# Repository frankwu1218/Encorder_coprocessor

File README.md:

# Encorder_coprocessor
Encoder coprocessor based on PICO2040

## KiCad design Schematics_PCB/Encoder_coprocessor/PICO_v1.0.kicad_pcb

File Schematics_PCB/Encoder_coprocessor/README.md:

# PICO_Encoder_sensor_PCB
Encoder sensor PCB board

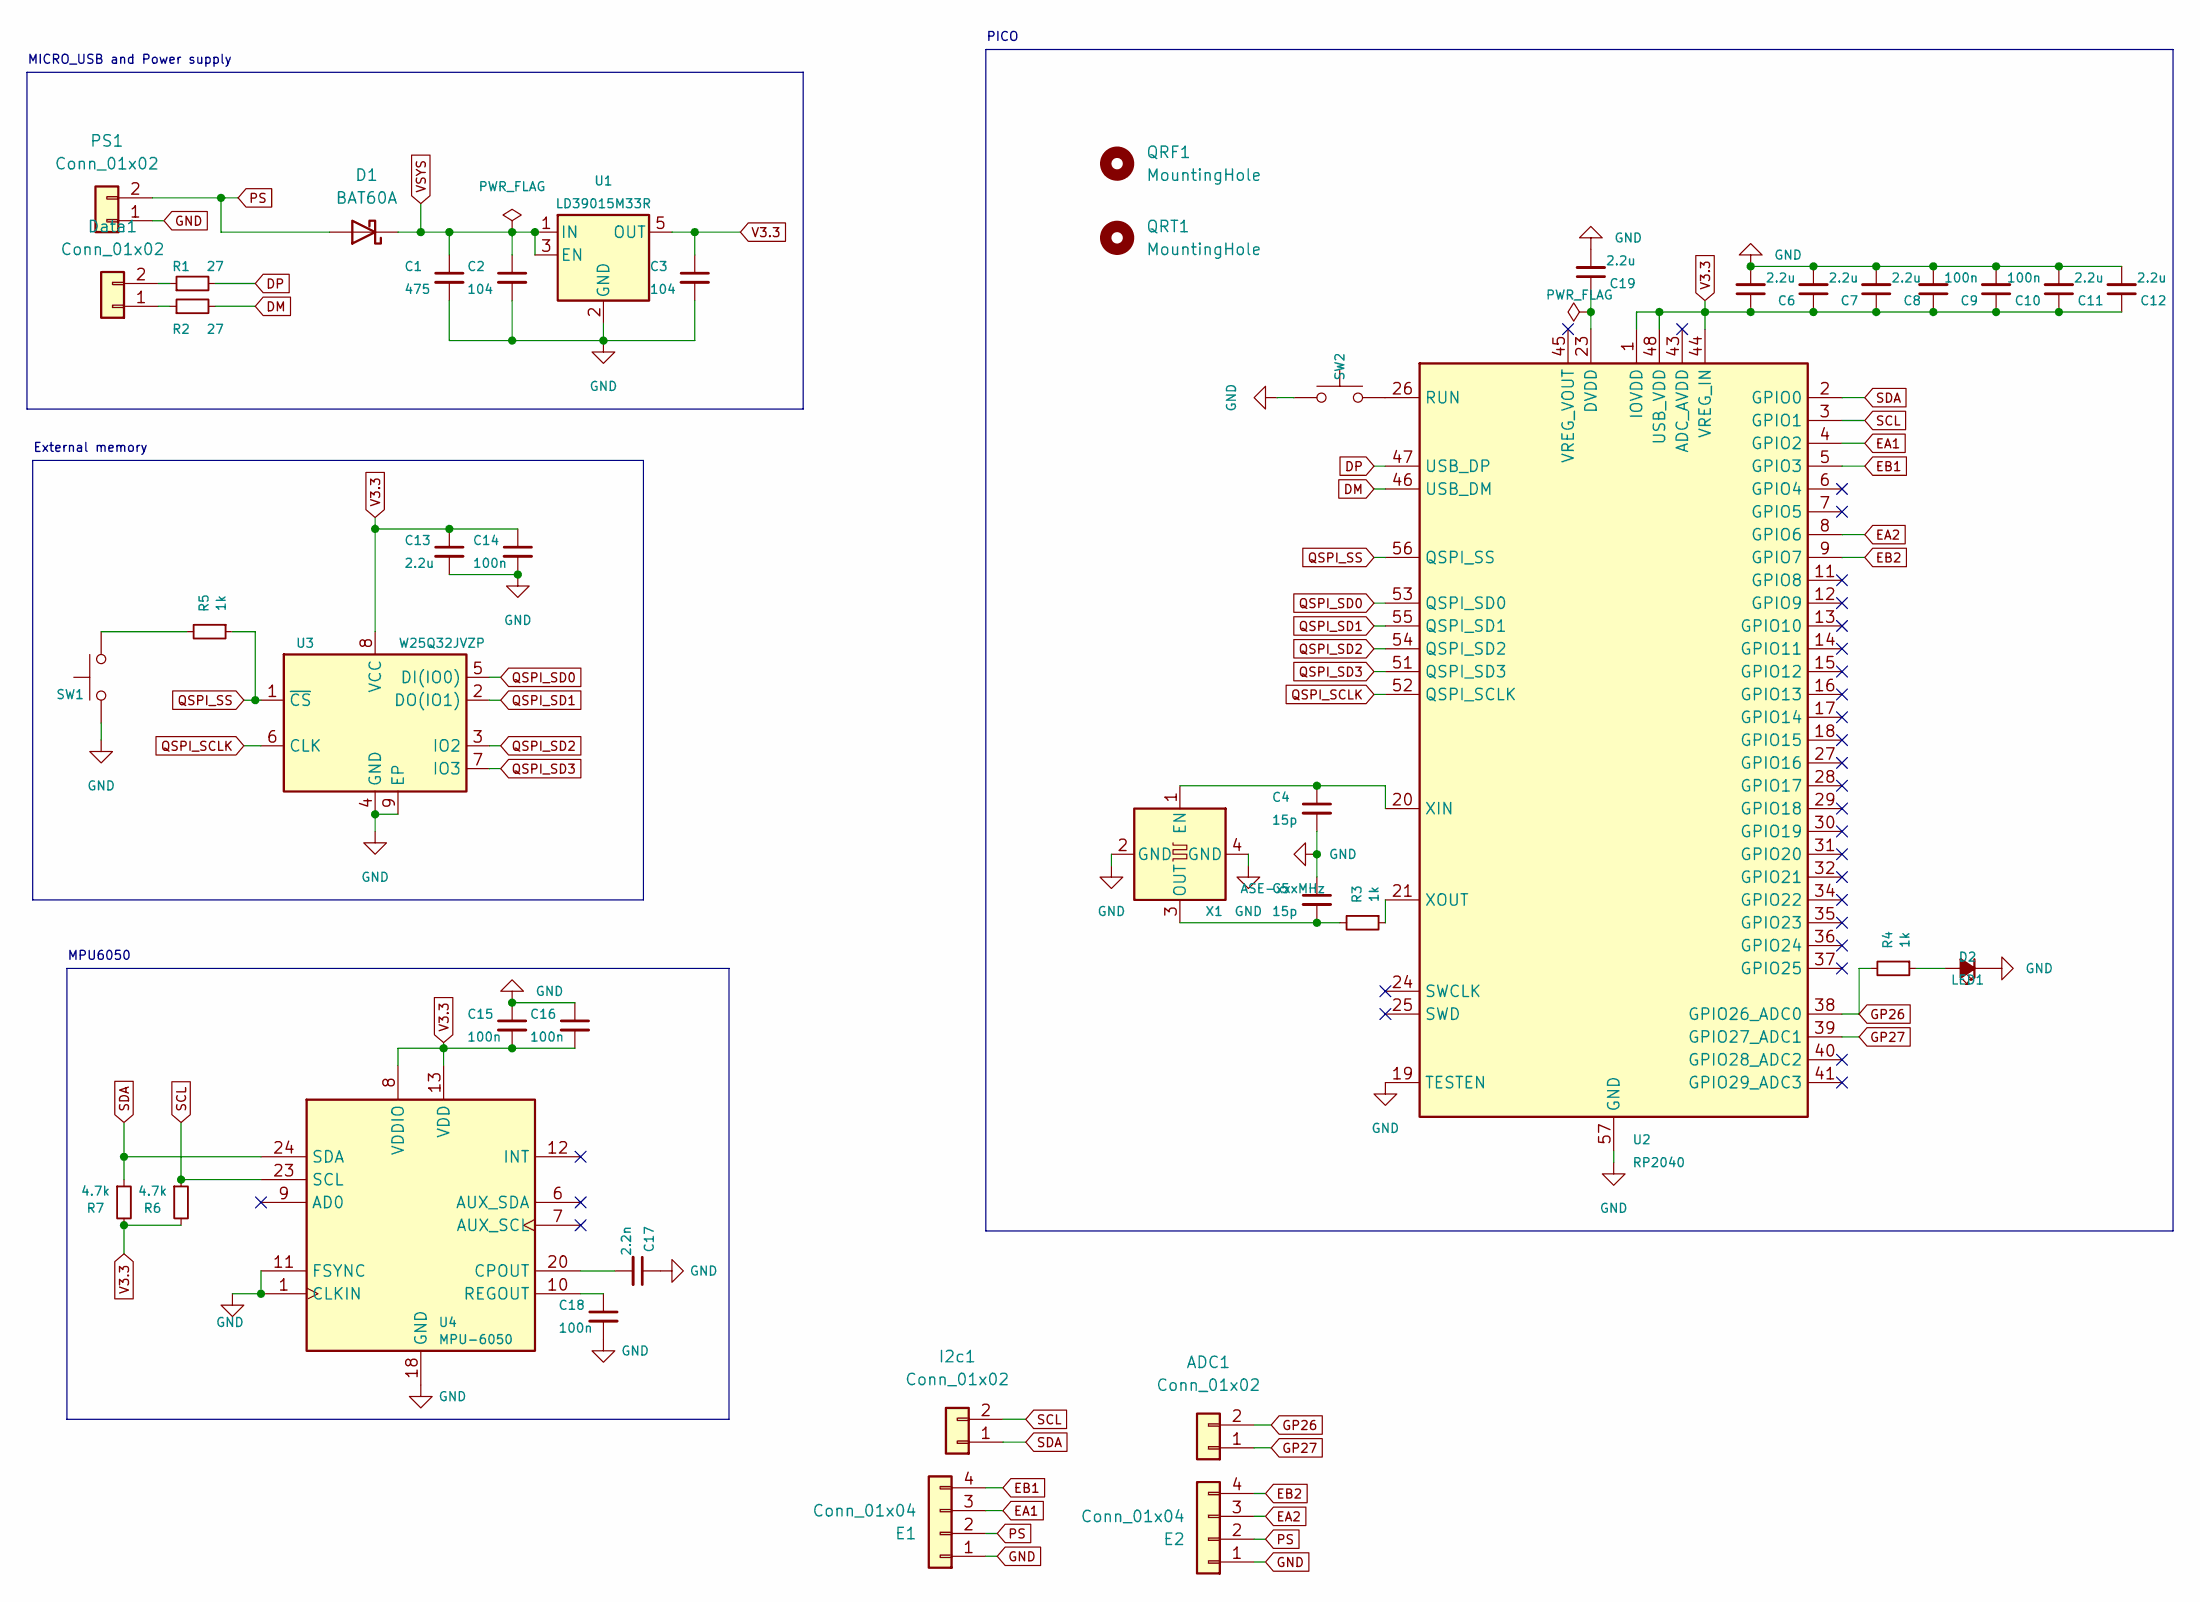
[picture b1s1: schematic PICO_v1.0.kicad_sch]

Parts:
ADC1: Conn_01x02; PinHeader_1x02_P2.54mm_Vertical
C1: 475; C_0603_1608Metric_Pad1.08x0.95mm_HandSolder
C2, C3: 104; C_0603_1608Metric_Pad1.08x0.95mm_HandSolder
C4, C5: 15p; C_0603_1608Metric_Pad1.08x0.95mm_HandSolder
C6, C7, C8, C11, C12, C13, C19: 2.2u; C_0603_1608Metric_Pad1.08x0.95mm_HandSolder
C9, C10, C14, C15, C16, C18: 100n; C_0603_1608Metric_Pad1.08x0.95mm_HandSolder
C17: 2.2n; C_0603_1608Metric_Pad1.08x0.95mm_HandSolder
D1: BAT60A; D_SOD-323
D2: LED1; LED_0603_1608Metric_Pad1.05x0.95mm_HandSolder
Data1: Conn_01x02; PinHeader_1x02_P2.54mm_Vertical
E1, E2: Conn_01x04; PinHeader_1x04_P2.54mm_Vertical
I2c1: Conn_01x02; PinHeader_1x02_P2.54mm_Vertical
PS1: Conn_01x02; PinHeader_1x02_P2.54mm_Vertical
QRF1: MountingHole; Frank_github_5_5
QRT1: MountingHole; Temple_5_5
R1, R2: 27; R_0603_1608Metric_Pad0.98x0.95mm_HandSolder
R3, R5: 1k; R_0603_1608Metric_Pad0.98x0.95mm_HandSolder
R4: 1k; R_0603_1608Metric
R6, R7: 4.7k; R_0603_1608Metric_Pad0.98x0.95mm_HandSolder
SW1, SW2: SW_Push; LED_1210_3225Metric_Pad1.42x2.65mm_HandSolder
U1: LD39015M33R; SOT-23-5
U2: RP2040; QFN-56-1EP_7x7mm_P0.4mm_EP3.2x3.2mm
U3: W25Q32JVZP; WSON-8-1EP_6x5mm_P1.27mm_EP3.4x4.3mm
U4: MPU-6050; InvenSense_QFN-24_4x4mm_P0.5mm
X1: ASE-xxxMHz; Oscillator_SMD_Abracon_ASE-4Pin_3.2x2.5mm

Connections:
DM: R2.2, U2.46 (USB_DM)
DP: R1.2, U2.47 (USB_DP)
EA1: E1.3, U2.4 (GPIO2)
EA2: E2.3, U2.8 (GPIO6)
EB1: E1.4, U2.5 (GPIO3)
EB2: E2.4, U2.9 (GPIO7)
GND: C1.2, C2.2, C3.2, C4.2, C5.1, C6.2, C7.2, C8.2, C9.2, C10.2, C11.2, C12.2, C13.2, C14.2, C15.1, C16.1, C17.1, C18.2, C19.2, D2.1 (K), E1.1, E2.1, PS1.1, SW1.1, SW2.1, U1.2 (GND), U2.19 (TESTEN), U2.57 (GND), U3.4 (GND), U3.9 (EP), U4.1 (CLKIN), U4.11 (FSYNC), U4.18 (GND), X1.2 (GND), X1.4 (GND)
GP26: ADC1.2, R4.2, U2.38 (GPIO26_ADC0)
GP27: ADC1.1, U2.39 (GPIO27_ADC1)
unnamed: C4.1, U2.20 (XIN), X1.1 (EN)
unnamed: C5.2, R3.2, X1.3 (OUT)
unnamed: C17.2, U4.20 (CPOUT)
unnamed: C18.1, U4.10 (REGOUT)
unnamed: C19.1, U2.23 (DVDD), U2.50 (DVDD)
unnamed: D2.2 (A), R4.1
unnamed: Data1.1, R2.1
unnamed: Data1.2, R1.1
unnamed: R3.1, U2.21 (XOUT)
unnamed: R5.2, SW1.2
unnamed: SW2.2, U2.26 (RUN)
PS: D1.2 (A), E1.2, E2.2, PS1.2
QSPI_SCLK: U2.52 (QSPI_SCLK), U3.6 (CLK)
QSPI_SD0: U2.53 (QSPI_SD0), U3.5 (DI(IO0))
QSPI_SD1: U2.55 (QSPI_SD1), U3.2 (DO(IO1))
QSPI_SD2: U2.54 (QSPI_SD2), U3.3 (IO2)
QSPI_SD3: U2.51 (QSPI_SD3), U3.7 (IO3)
QSPI_SS: R5.1, U2.56 (QSPI_SS), U3.1 (~CS)
SCL: I2c1.2, R6.1, U2.3 (GPIO1), U4.23 (SCL)
SDA: I2c1.1, R7.1, U2.2 (GPIO0), U4.24 (SDA)
V3.3: C3.1, C6.1, C7.1, C8.1, C9.1, C10.1, C11.1, C12.1, C13.1, C14.1, C15.2, C16.2, R6.2, R7.2, U1.5 (OUT), U2.1 (IOVDD), U2.10 (IOVDD), U2.22 (IOVDD), U2.33 (IOVDD), U2.42 (IOVDD), U2.44 (VREG_IN), U2.48 (USB_VDD), U2.49 (IOVDD), U3.8 (VCC), U4.8 (VDDIO), U4.13 (VDD)
VSYS: C1.1, C2.1, D1.1 (K), U1.1 (IN), U1.3 (EN)

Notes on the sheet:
MPU6050
MICRO_USB and Power supply
External memory
PICO

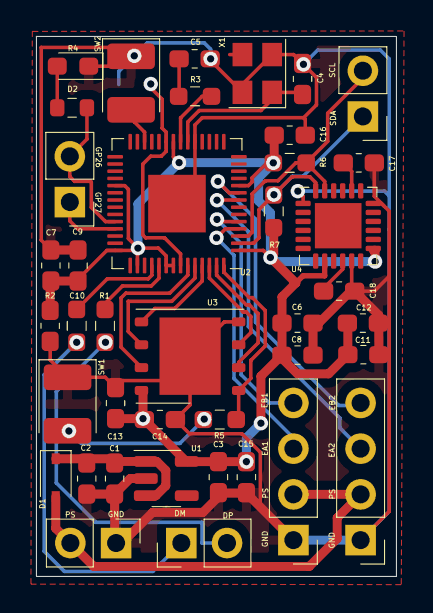
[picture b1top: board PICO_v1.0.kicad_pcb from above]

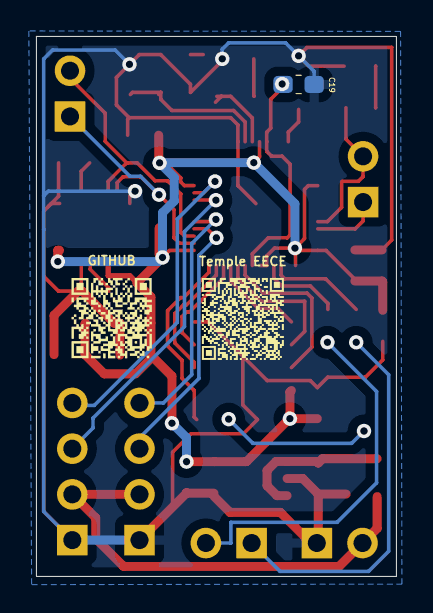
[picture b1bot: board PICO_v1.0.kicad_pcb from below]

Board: 2 copper layers, 20.0 x 30.0 mm, 43 parts (3 on the bottom side), 31 nets.

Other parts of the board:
GITHUB: MountingHole; Frank_github_5_5
Temple EECE: MountingHole; Temple_5_5

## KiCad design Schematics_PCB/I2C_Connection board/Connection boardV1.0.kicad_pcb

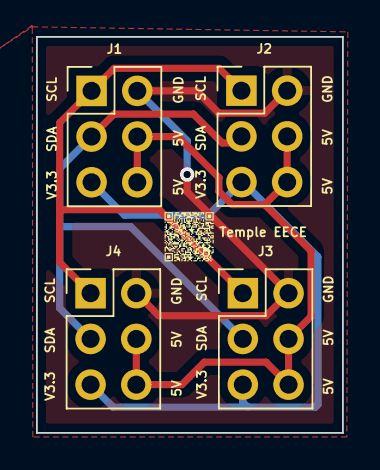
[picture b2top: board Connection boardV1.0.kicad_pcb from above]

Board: 2 copper layers, 17.0 x 22.0 mm, 6 parts (1 on the bottom side), 5 nets.

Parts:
GITHUB: MountingHole; Git_3_3
J1, J2, J3, J4: Conn_02x03_Odd_Even; PinHeader_2x03_P2.54mm_Vertical
Temple EECE: MountingHole; Temple_3_3

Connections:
3.3V: J1.5, J2.5, J3.5, J4.5
5V: J1.4, J1.6, J2.4, J2.6, J3.4, J3.6, J4.4, J4.6
GND: J1.2, J2.2, J3.2, J4.2
SCL: J1.1, J2.1, J3.1, J4.1
SDA: J1.3, J2.3, J3.3, J4.3
